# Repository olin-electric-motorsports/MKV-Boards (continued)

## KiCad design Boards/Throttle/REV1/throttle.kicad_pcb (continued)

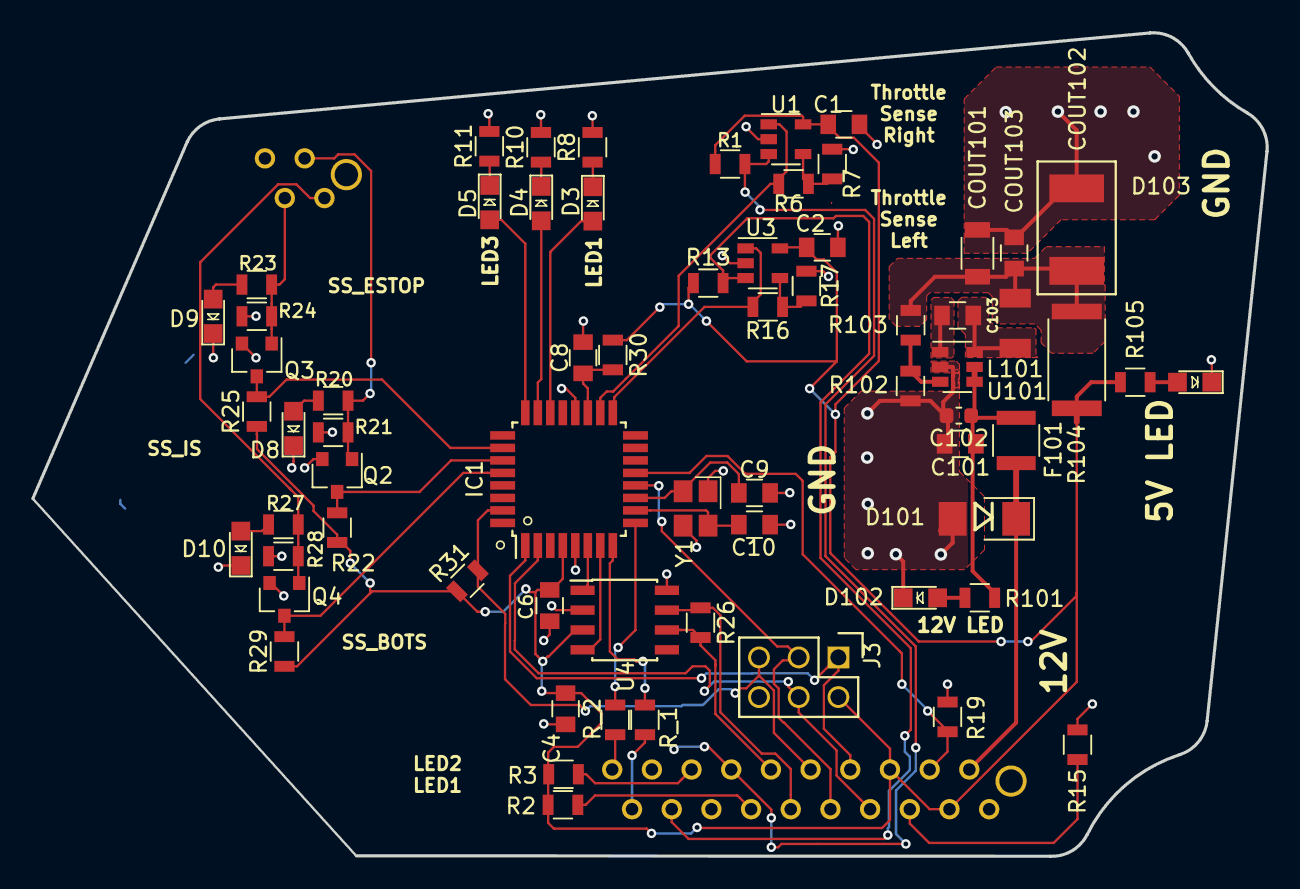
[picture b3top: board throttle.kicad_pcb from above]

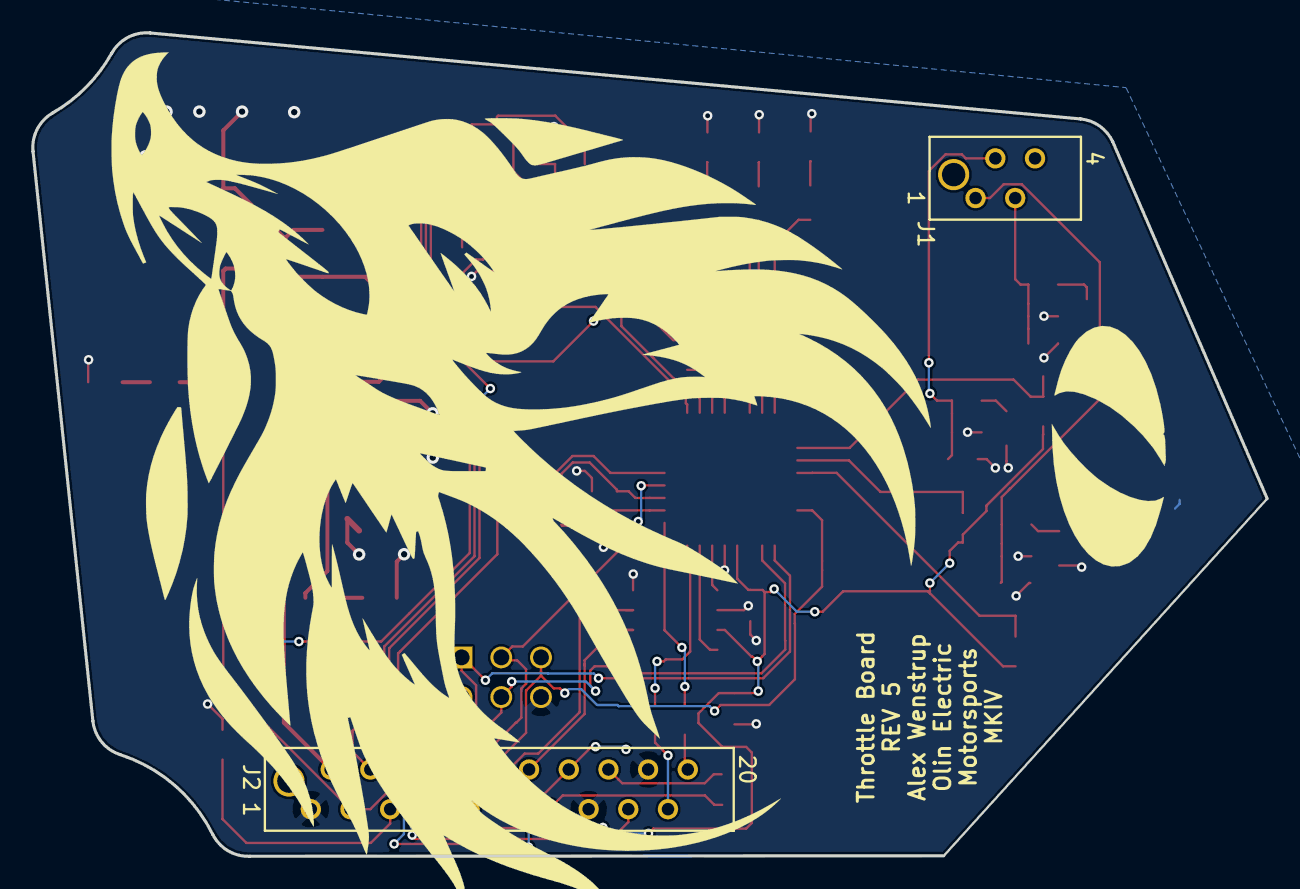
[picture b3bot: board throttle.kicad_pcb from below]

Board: 2 copper layers, 79.0 x 52.7 mm, 68 parts (2 on the bottom side), 50 nets.

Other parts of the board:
R2, R3: R_0; R_0805_OEM

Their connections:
unnamed 54: R2.1; also elsewhere on the board
unnamed 55: R3.2; also elsewhere on the board
VCC: R2.2, R3.1; also elsewhere on the board
